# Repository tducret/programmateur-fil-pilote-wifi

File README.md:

Le programmateur fil pilote WiFi open source
============================================

Principe
--------
Avec de simples requêtes HTTP, vous allez pouvoir :
- **Contrôler vos chauffages électriques** (7 zones / 4 ordres fil pilote)
- **Récupérer votre consommation électrique** (et toutes les informations du compteur électrique)

Avantages :
- **Pas de serveur dédié nécessaire**
- **Intégration facile dans le tableau électrique**
- **Connexion WiFi** (pas de câble Ethernet à connecter)

Idées d'applications
--------------------
- Contrôle de la température de chaque pièce via votre box domotique
- Coupure du chauffage automatique en cas de consommation électrique trop importante (délestage)
- Lancement du chauffage en partant du travail à partir de votre smartphone
- Et bien d'autres...

Licence
-------
Les codes sources sont distribués sous la licence MIT
Les autres éléments sont distribués sous la licence [Creative Commons Attribution-NonCommercial-ShareAlike 4.0](https://creativecommons.org/licenses/by-nc-sa/4.0/)

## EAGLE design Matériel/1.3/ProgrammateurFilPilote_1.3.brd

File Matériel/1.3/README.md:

Version matérielle 1.3
=======================

Modifications
-------------
Cette version reprend toutes les caractéristiques de la version [initiale][1] en y ajoutant les fonctionnalités suivantes :

- Ajout d'un contrôleur d'entrées sortie I2C [MCP23017][10] pour libérer les I/O du Spark Core
- Possibilité de mettre deux types de relais dont un [avec contact NO + NF][5]
- Possibilité de mettre un emetteur récepteur sans fil de type [RFM12B][6], [RFM69CW][7], [RFM69HW][8] ou [RFM69CW][9] 433Mhz ou 868MHz
- Possibilité de mettre un [récepteur 433MHz][4] pour récupérer par exemple les trames des capteurs de température Orégon Scientific
- Ajout d'un connecteur I2C ET SPI pour des afficheurs OLED de type [I2C][2] ou [SPI][3]
- Ajout d'un connecteur de type Grove I2C
- Ajout d'une LED 3mm (déportable ou non) sur le boitier 
- Ajout de pin out disponibles sur toutes les pattes du Spark Core

Changements apportés dans la révision 1.3 vs 1.2 
- Ajout d'un étage a MOSFET pour la téléinfo, pour une meilleure compatibilité di signal téléinfo
- Ajout d'une RGB LED pour ESP8266
- Ajout d'un pont diviseur sur le recepteur 433MHZ pour transformer sa sortie 5V en 3V3 pour l'ESP8266
- Possibilité de mettre une base ESP8266 (NodeMCU) via cet [adaptateur][11]

Description Détaillée
=====================

**Schematic**  

**Boards**  
&nbsp;
&nbsp;

[1]: https://github.com/thibdct/programmateur-fil-pilote-wifi/blob/master/README.md
[2]: http://www.ebay.com/itm/291216700457
[3]: http://www.ebay.com/itm/141371873602
[4]: http://www.ebay.com/itm/290935235157
[5]: http://www.seeedstudio.com/depot/index.php?main_page=opl_info&opl_id=136

[6]: http://www.anarduino.com/details.jsp?pid=142
[7]: http://www.anarduino.com/details.jsp?pid=145
[8]: http://www.anarduino.com/details.jsp?pid=136
[9]: http://www.anarduino.com/details.jsp?pid=122
[10]: http://www.adafruit.com/product/732
[11]: https://github.com/hallard/Particle2NodeMCU

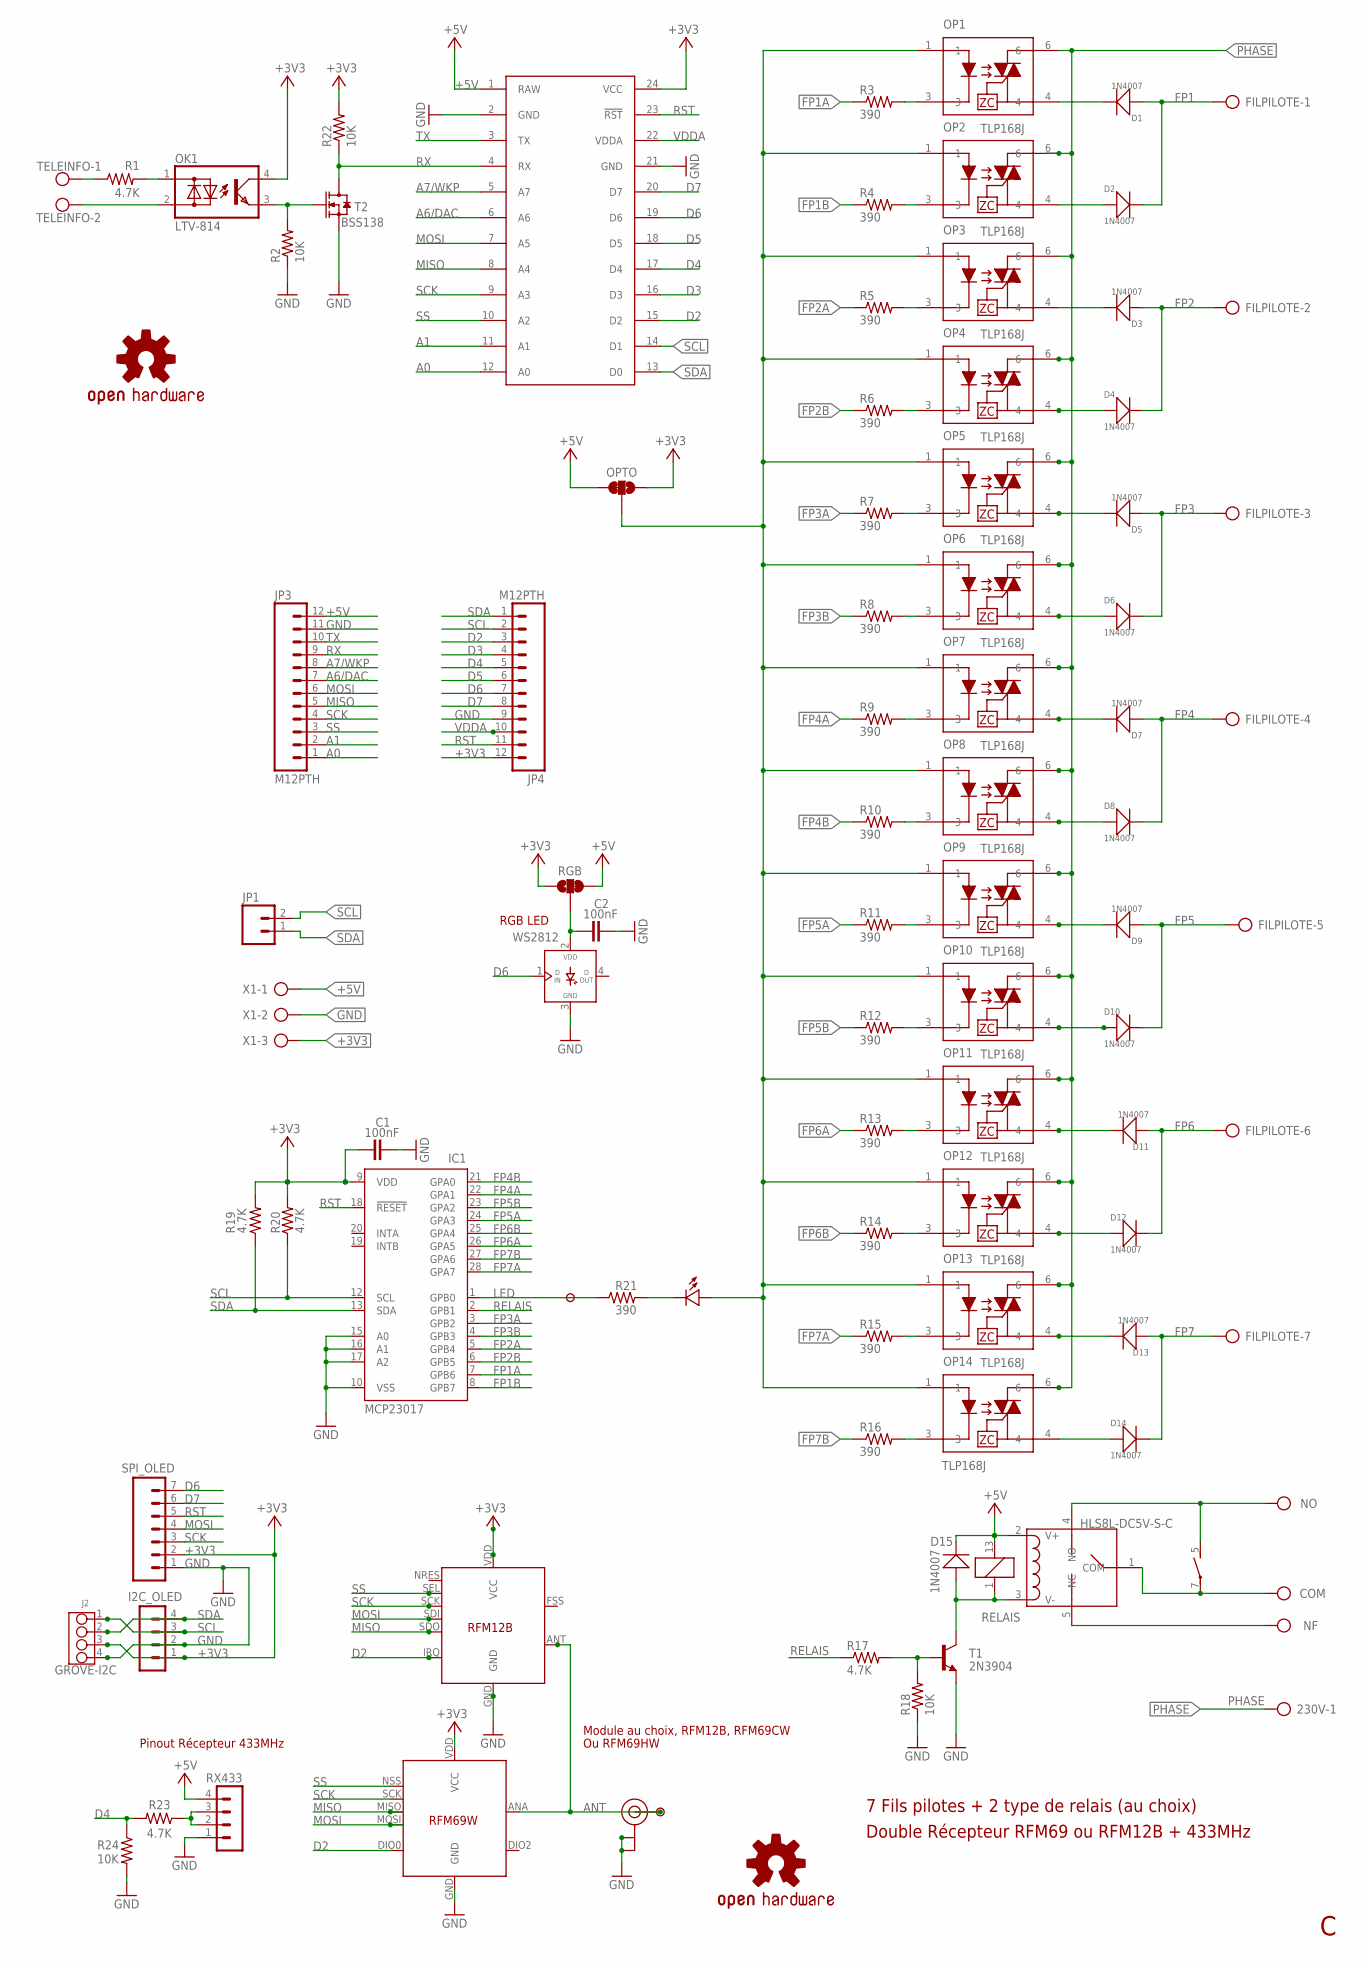
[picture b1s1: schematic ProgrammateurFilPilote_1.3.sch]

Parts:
230V: AK500/2
C1, C2: 100nF; 1206-CAP
D1, D2, D3, D4, D5, D6, D7, D8, D9, D10, D11, D12, D13, D14, D15: 1N4007; DO-214AC
FILPILOTE: AK500/7
I2C_OLED: CON_HEADER_1X04'SMALL''; M1X4
IC1: MCP23017; DIL28-3
J2: GROVE-I2C; 4P-2.0
JP1: M02PTH; 1X02
JP3, JP4: M12PTH; 1X12-SMALL-PADS
LED: LED3MM
LOGO1, LOGO2: OSHW-LOGOL; OSHW-LOGO-L
OK1: LTV-814; DIL4-SMD
OP1, OP2, OP3, OP4, OP5, OP6, OP7, OP8, OP9, OP10, OP11, OP12, OP13, OP14: TLP168J; MFSOP-4-HANDSOLDER
OPTO: JUMPER-PAD-3-2OF3_NC_BY_TRACE_LARGE; PAD-JUMPER-3-2OF3_NC_BY_TRACE_YES_SILK_LARGE
P1, P2: PADSMALL; PAD-SMALL
PARTICLE: Spark/Photon; SPARK_CORE
R1, R17, R19, R20, R23: 4.7K; 1206-RES
R2, R18, R22, R24: 10K; 1206-RES
R3, R4, R5, R6, R7, R8, R9, R10, R11, R12, R13, R14, R15, R16, R21: 390; 1206-RES
RELAIS: Relais G6D; G6D
RGB: JUMPER-PAD-3-2OF3_NC_BY_TRACE_SMALL; PAD-JUMPER-3-2OF3_NC_BY_TRACE_YES_SILK_FULL_BOX
RL: AK500/2
RX433: CON_HEADER_1X04'NO_LOCK'; 1X04_NO_LOCK
SPI_OLED: CON_HEADER_1X07'SMALL'; M1X7
SW1: HLS8L-DC5V-S-C; 5P-L19.0XW15.0XH15.0MM
T1: 2N3904; TO92-EBC
T2: BSS138; SOT23
TELEINFO: AK500/2
U$2: RFM12B; RFM12B-MINPADS
U$3: RFM69W; RFM69W-MINPADS
U-FL: U.FL
WS2812: RGB LED; WS2812-PTH
X1: AK500/3

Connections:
+3V3: C1.1, I2C_OLED.1, IC1.9 (VDD), J2.3, JP4.12, OK1.4 (C), OPTO.1, PARTICLE.24 (VCC), R19.2, R20.2, R22.2, RGB.1, SPI_OLED.2, U$2.VDD (VCC), U$3.VDD (VCC), X1.3
+5V: D15.2 (-), JP3.12, OPTO.3, PARTICLE.1 (RAW), RELAIS.13 (2), RGB.3, RX433.4, SW1.2 (V+), X1.1
A0: JP3.1, PARTICLE.12 (A0)
A1: JP3.2, PARTICLE.11 (A1)
A6/DAC: JP3.7, PARTICLE.6 (A6)
A7/WKP: JP3.8, PARTICLE.5 (A7)
ANT: P1.1, U$2.ANT, U$3.ANA (ANT), U-FL.3 (SIGNAL)
COM: RELAIS.7, RL.1, SW1.1 (COM)
D2: JP4.3, PARTICLE.15 (D2), U$2.IRQ, U$3.DIO0
D3: JP4.4, PARTICLE.16 (D3)
D4: JP4.5, PARTICLE.17 (D4), R23.2, R24.1
D5: JP4.6, PARTICLE.18 (D5)
D6: JP4.7, PARTICLE.19 (D6), SPI_OLED.7, WS2812.1 (DIN)
D7: JP4.8, PARTICLE.20 (D7), SPI_OLED.6
FP1: D1.1 (+), D2.2 (-), FILPILOTE.1
FP1A: IC1.7 (GPB6), R3.1
FP1B: IC1.8 (GPB7), R4.1
FP2: D3.1 (+), D4.2 (-), FILPILOTE.2
FP2A: IC1.5 (GPB4), R5.1
FP2B: IC1.6 (GPB5), R6.1
FP3: D5.1 (+), D6.2 (-), FILPILOTE.3
FP3A: IC1.3 (GPB2), R7.1
FP3B: IC1.4 (GPB3), R8.1
FP4: D7.1 (+), D8.2 (-), FILPILOTE.4
FP4A: IC1.22 (GPA1), R9.1
FP4B: IC1.21 (GPA0), R10.1
FP5: D9.1 (+), D10.2 (-), FILPILOTE.5
FP5A: IC1.24 (GPA3), R11.1
FP5B: IC1.23 (GPA2), R12.1
FP6: D11.1 (+), D12.2 (-), FILPILOTE.6
FP6A: IC1.26 (GPA5), R13.1
FP6B: IC1.25 (GPA4), R14.1
FP7: D13.1 (+), D14.2 (-), FILPILOTE.7
FP7A: IC1.28 (GPA7), R15.1
FP7B: IC1.27 (GPA6), R16.1
GND: C1.2, C2.2, I2C_OLED.2, IC1.10 (VSS), IC1.15 (A0), IC1.16 (A1), IC1.17 (A2), J2.4, JP3.11, JP4.9, PARTICLE.2 (GND), PARTICLE.21 (GND), R2.1, R18.1, R24.2, RX433.1, SPI_OLED.1, T1.E, T2.2 (S), U$2.GND, U$3.GND, U-FL.1 (GND), U-FL.2 (GND), WS2812.3 (GND), X1.2
LED: IC1.1 (GPB0), P2.1, R21.1
MISO: JP3.5, PARTICLE.8 (A4), U$2.SDO, U$3.MISO
MOSI: JP3.6, PARTICLE.7 (A5), SPI_OLED.4, U$2.SDI, U$3.MOSI
unnamed: D1.2 (-), OP1.4
unnamed: D2.1 (+), OP2.4
unnamed: OK1.2 (AC2), TELEINFO.2
unnamed: OK1.1 (AC1), R1.2
unnamed: R1.1, TELEINFO.1
unnamed: LED.MINUS, R21.2
unnamed: OP1.3, R3.2
unnamed: OP2.3, R4.2
unnamed: OP3.3, R5.2
unnamed: OP4.3, R6.2
unnamed: OP5.3, R7.2
unnamed: OP6.3, R8.2
unnamed: OP7.3, R9.2
unnamed: OP8.3, R10.2
unnamed: D15.1 (+), RELAIS.1, SW1.3 (V-), T1.C
unnamed: C2.1, RGB.2, WS2812.2 (VDD)
unnamed: OK1.3 (E), R2.2, T2.1 (G)
unnamed: OP9.3, R11.2
unnamed: LED.PLUS, OP1.1, OP2.1, OP3.1, OP4.1, OP5.1, OP6.1, OP7.1, OP8.1, OP9.1, OP10.1, OP11.1, OP12.1, OP13.1, OP14.1, OPTO.2
unnamed: R17.2, R18.2, T1.B
unnamed: D3.2 (-), OP3.4
unnamed: D5.2 (-), OP5.4
unnamed: D4.1 (+), OP4.4
unnamed: D7.2 (-), OP7.4
unnamed: D6.1 (+), OP6.4
unnamed: D8.1 (+), OP8.4
unnamed: OP10.3, R12.2
unnamed: OP14.3, R16.2
unnamed: D9.2 (-), OP9.4
unnamed: OP11.3, R13.2
unnamed: OP12.3, R14.2
unnamed: D10.1 (+), OP10.4
unnamed: D12.1 (+), OP12.4
NF: RL.2, SW1.5 (NC)
NO: 230V.2, RELAIS.5 (S), SW1.4 (NO)
PHASE: 230V.1, OP1.6, OP2.6, OP3.6, OP4.6, OP5.6, OP6.6, OP7.6, OP8.6, OP9.6, OP10.6, OP11.6, OP12.6, OP13.6, OP14.6
RELAIS: IC1.2 (GPB1), R17.1
RST: IC1.18 (!RESET), JP4.11, PARTICLE.23 (!RST), SPI_OLED.5
RX: JP3.9, PARTICLE.4 (RX), R22.1, T2.3 (D)
RX433: R23.1, RX433.2, RX433.3
S$1: D11.2 (-), OP11.4
S$3: D13.2 (-), OP13.4
S$5: OP13.3, R15.2
S$11: D14.1 (+), OP14.4
SCK: JP3.4, PARTICLE.9 (A3), SPI_OLED.3, U$2.SCK, U$3.SCK
SCL: I2C_OLED.3, IC1.12 (SCL), J2.1, JP1.2, JP4.2, PARTICLE.14 (D1), R20.1
SDA: I2C_OLED.4, IC1.13 (SDA), J2.2, JP1.1, JP4.1, PARTICLE.13 (D0), R19.1
SS: JP3.3, PARTICLE.10 (A2), U$2.SEL, U$3.NSS (SEL)
TX: JP3.10, PARTICLE.3 (TX)
VDDA: JP4.10, PARTICLE.22 (VDDA)

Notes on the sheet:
7 Fils pilotes + 2 type de relais (au choix)
Module au choix, RFM12B, RFM69CW
Ou RFM69HW
Pinout Récepteur 433MHz
Double Récepteur RFM69 ou RFM12B + 433MHz
RGB LED

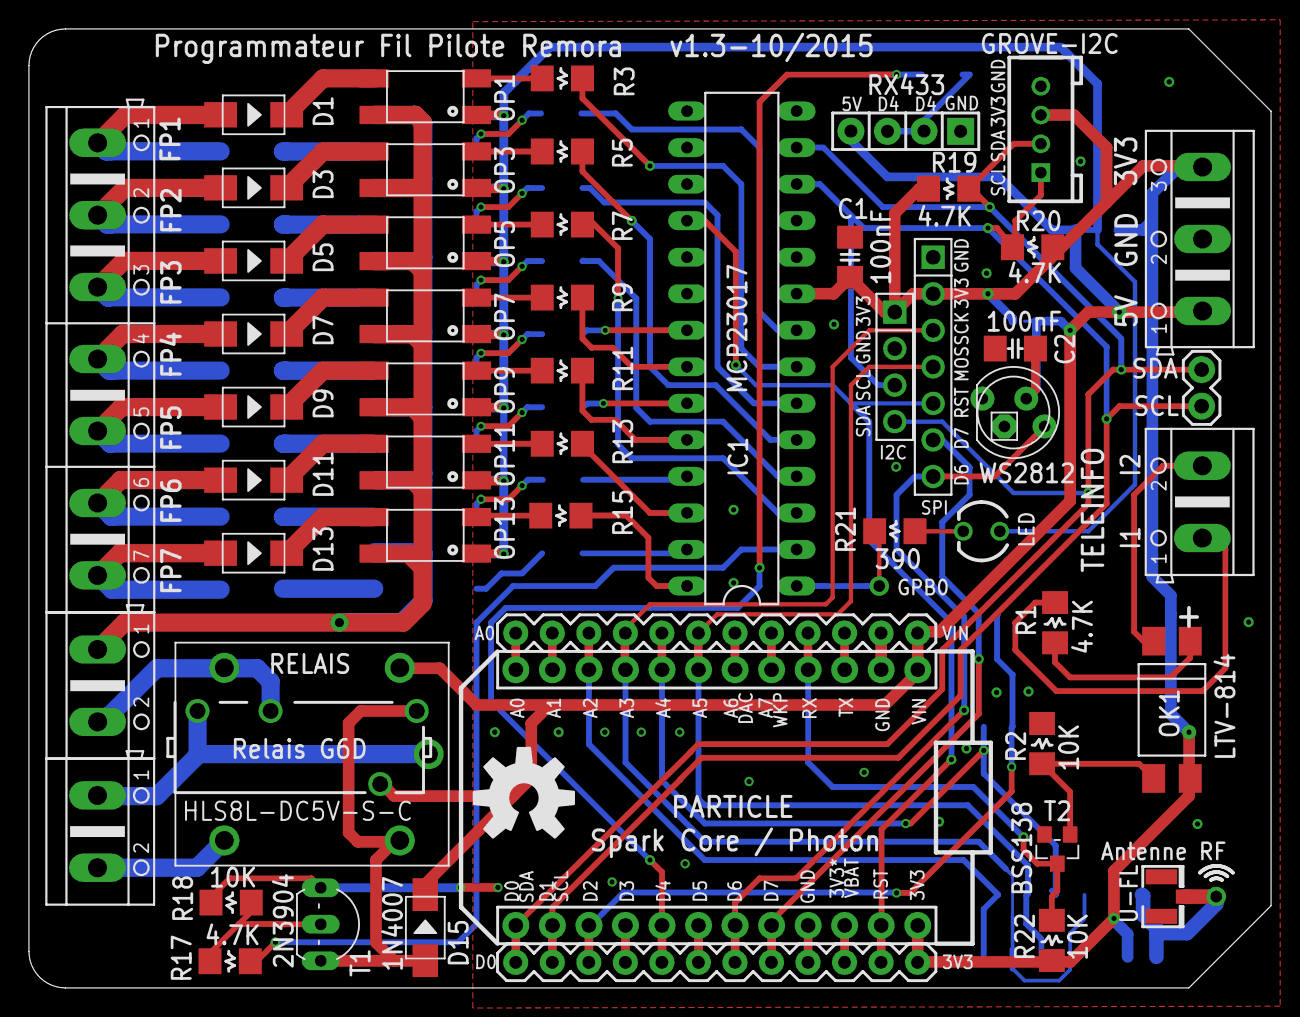
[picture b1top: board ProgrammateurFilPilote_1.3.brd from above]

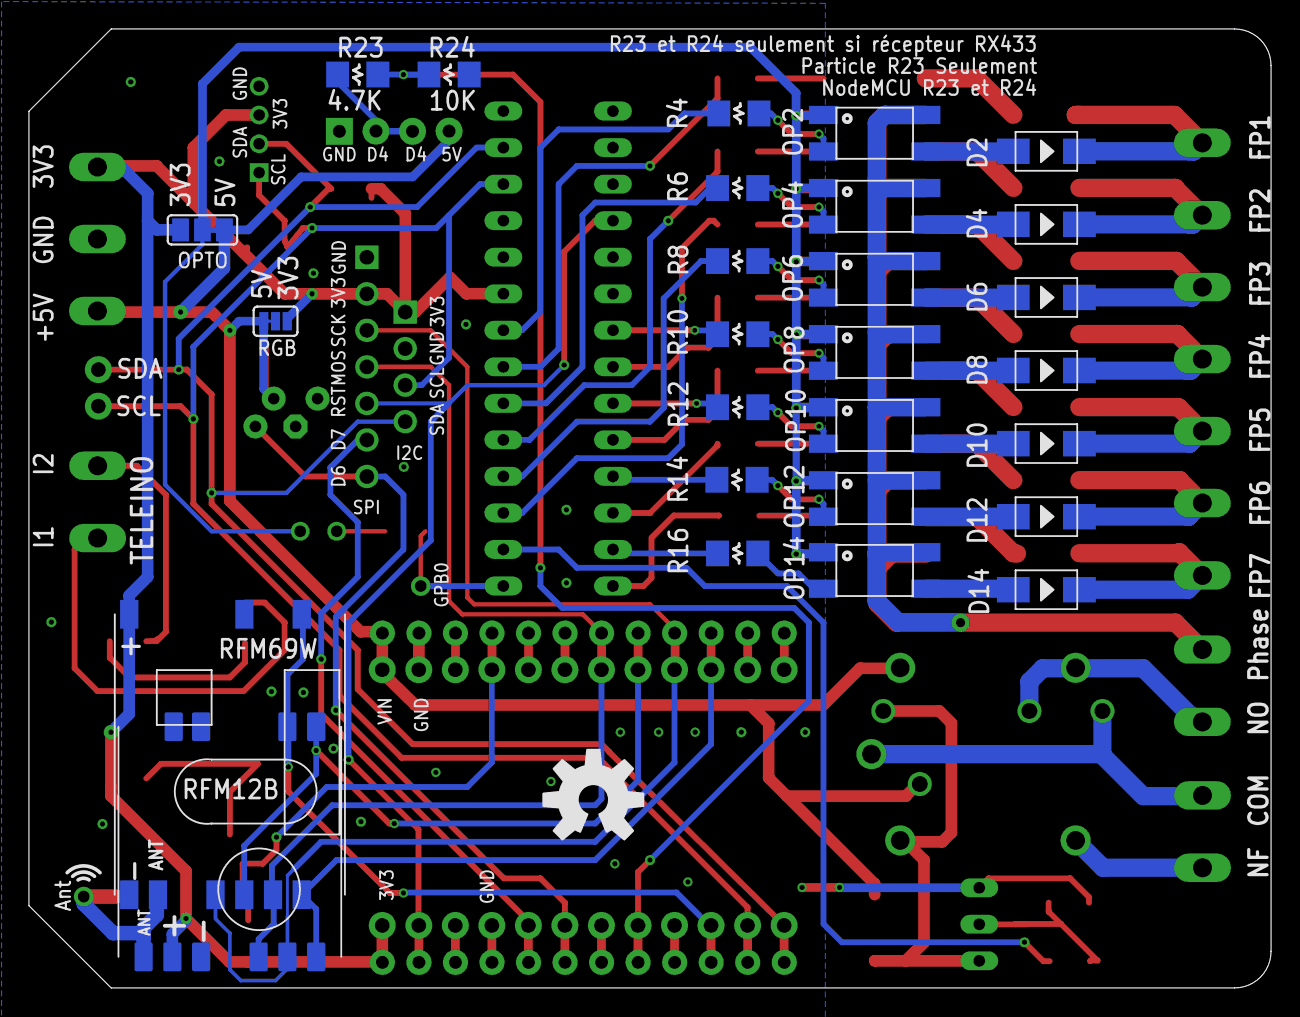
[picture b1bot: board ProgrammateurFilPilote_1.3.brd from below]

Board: 2 copper layers, 86.4 x 66.7 mm, 85 parts (28 on the bottom side), 89 nets.

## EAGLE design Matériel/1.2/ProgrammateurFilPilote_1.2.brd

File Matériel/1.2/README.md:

Version matérielle 1.2c
=======================

Modifications
-------------
Cette version reprend toutes les caractéristiques de la version [initiale][1] en y ajoutant les fonctionnalités suivantes :

- Ajout d'un contrôleur d'entrées sortie I2C [MCP23017][10] pour libérer les I/O du Spark Core
- Possibilité de mettre deux types de relais dont un [avec contact NO + NF][5]
- Possibilité de mettre un emetteur récepteur sans fil de type [RFM12B][6], [RFM69CW][7], [RFM69HW][8] ou [RFM69CW][9] 433Mhz ou 868MHz
- Possibilité de mettre un [récepteur 433MHz][4] pour récupérer par exemple les trames des capteurs de température Orégon Scientific
- Ajout d'un connecteur I2C ET SPI pour des afficheurs OLED de type [I2C][2] ou [SPI][3]
- Ajout d'un connecteur de type Grove I2C
- Ajout d'une LED 3mm (déportable ou non) sur le boitier 
- Ajout de pin out disponibles sur toutes les pattes du Spark Core

Changements apportés dans la révision 1.2c 
- Correction informations du silk au niveau du connecteur grove
- Déplacement connecteur grove pour ne pas géner en cas d'insertion un module grove
- Déplacement de la LED pour qu'elle ne soit plus située sous le LCD
- Agrandissement des PAD des optos pour une soudure plus aisée
- Inversion des plots 3.3V et GND afin de pouvoir souder un double plot uniquement (5V+GND), les triples étant moins facile à trouver et je suis pas certain que le 3.3V soit utilisé (mais il reste disponible)

Attention, deux erreurs étaient présentes sur le PCB 1.2 original (corrigées dans la revision 1.2c) :
- le dessin sur le PCB du connecteur grove est inversé, donc si vous souhaitez le souder, il faut le faire dans le sens inversé par rapport au dessin du PCB (mais toujours à souder sur le dessus).
- la diode D14 est inversée, il faut donc la souder dans le sens inverse de ce qui est indiqué sur le PCB

Description Détaillée
=====================

**Schematic**  

**Boards**  
&nbsp;
&nbsp;

[1]: https://github.com/thibdct/programmateur-fil-pilote-wifi/blob/master/README.md
[2]: http://www.ebay.com/itm/291216700457
[3]: http://www.ebay.com/itm/141371873602
[4]: http://www.ebay.com/itm/290935235157
[5]: http://www.seeedstudio.com/depot/index.php?main_page=opl_info&opl_id=136

[6]: http://www.anarduino.com/details.jsp?pid=142
[7]: http://www.anarduino.com/details.jsp?pid=145
[8]: http://www.anarduino.com/details.jsp?pid=136
[9]: http://www.anarduino.com/details.jsp?pid=122
[10]: http://www.adafruit.com/product/732

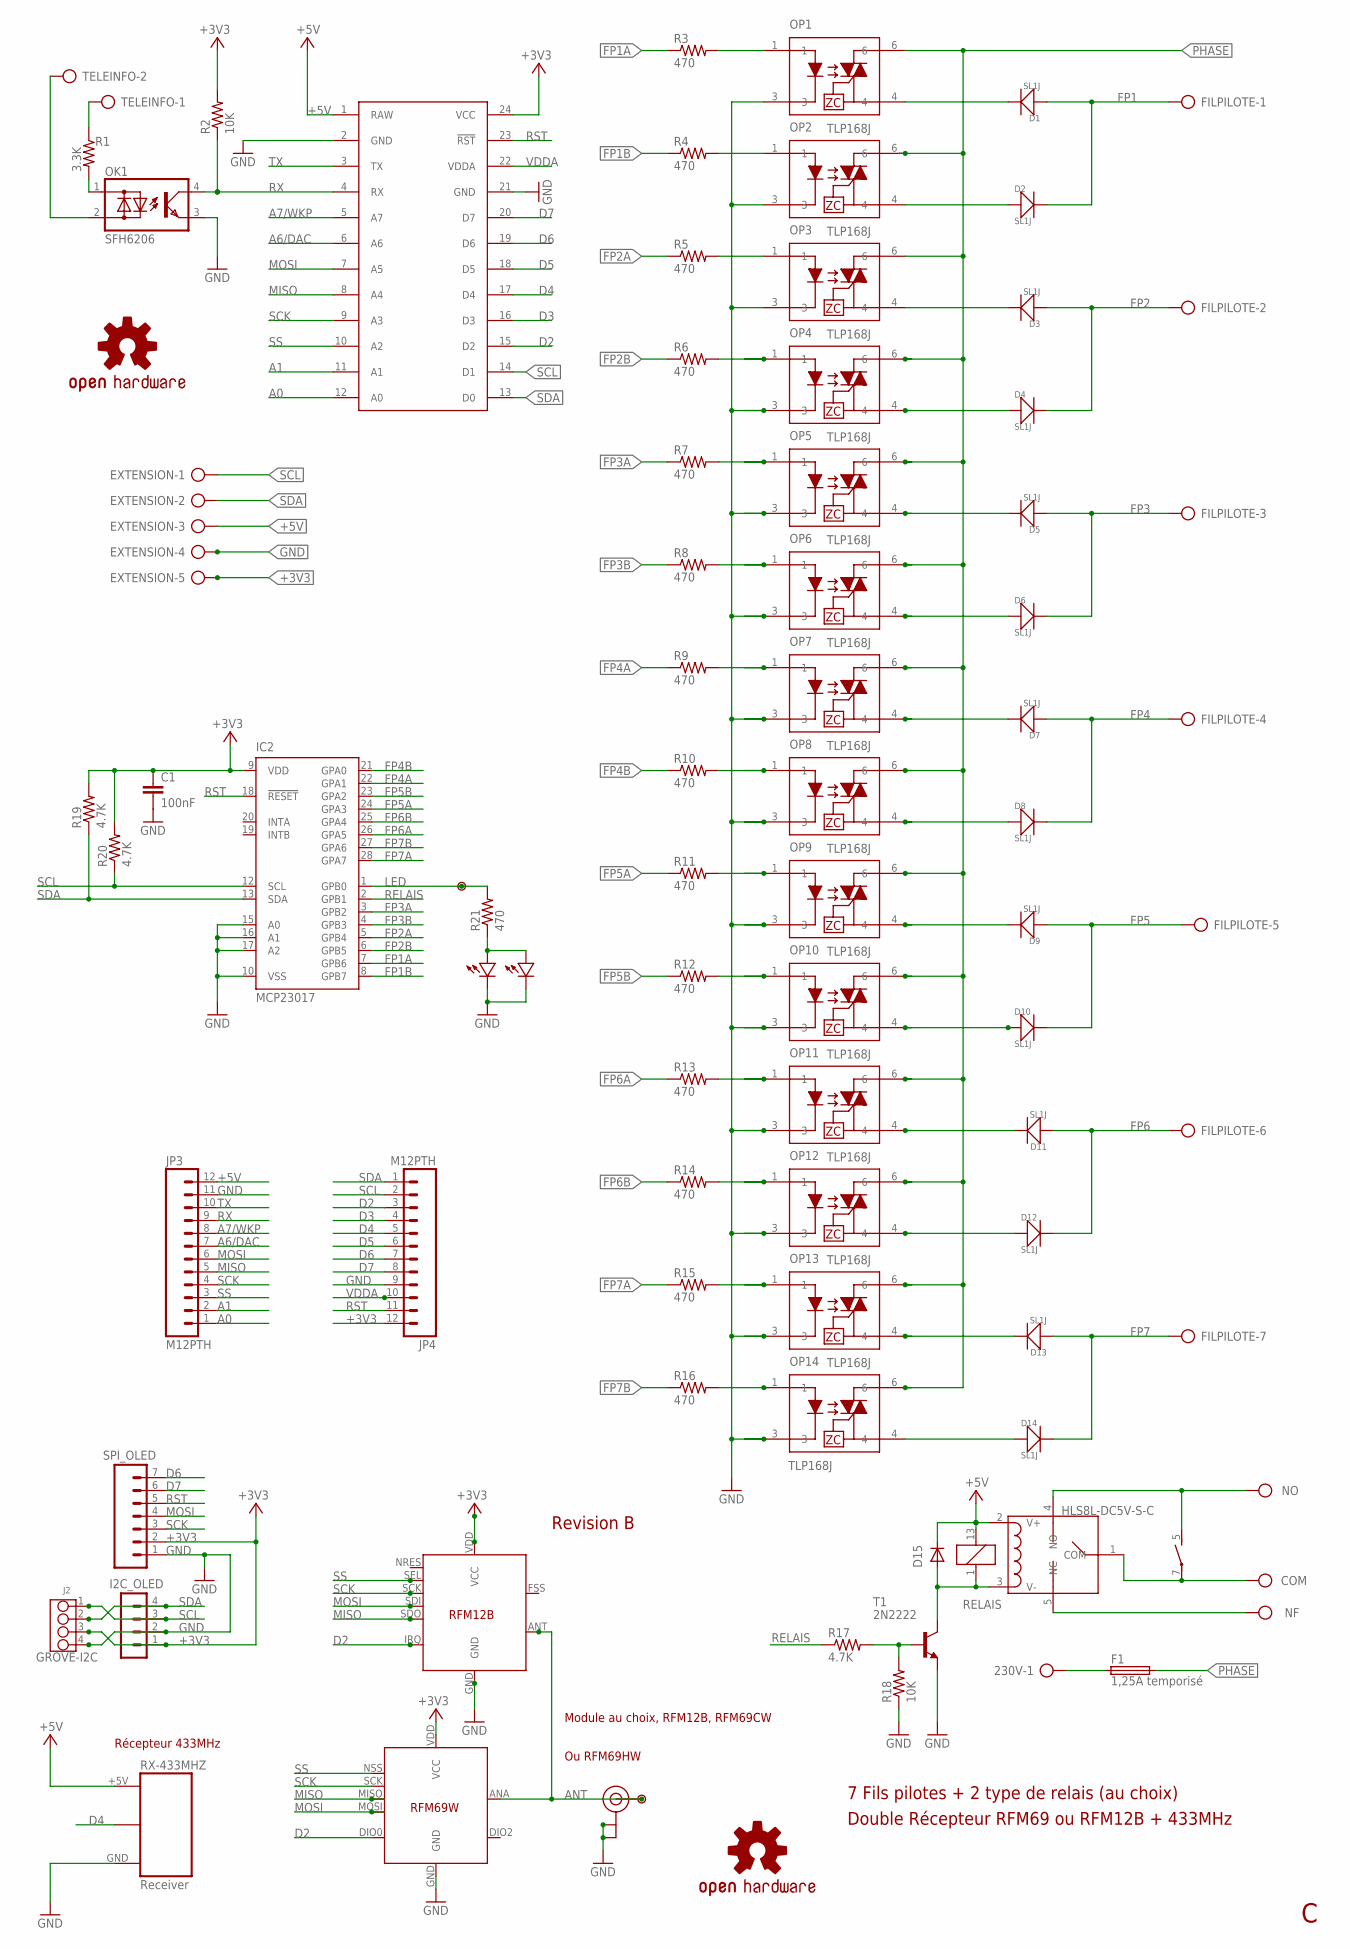
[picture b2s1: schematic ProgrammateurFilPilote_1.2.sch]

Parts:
230V: AK500/2
C1: 100nF; 1206-CAP
D1, D2, D3, D4, D5, D6, D7, D8, D9, D10, D11, D12, D13, D14: SL1J; DO-214AC
D15: CGRM4001-G; SOD-123_MINI-SMA
EXTENSION: AK500/5
F1: 1,25A temporisé; TE5
FILPILOTE: AK500/7
I2C_OLED: CON_HEADER_1X04'SMALL''; M1X4
IC2: MCP23017; DIL28-3
J2: GROVE-I2C; 4P-2.0
JP3, JP4: M12PTH; 1X12-SMALL-PADS
L: LED0805-LARGE; 0805-LED-LARGEPADS
LED: LED3MMNOSILK; LED3MM_NOSILK
LOGO1, LOGO2: OSHW-LOGOL; OSHW-LOGO-L
OK1: SFH6206; DIL4-SMD
OP1, OP2, OP3, OP4, OP5, OP6, OP7, OP8, OP9, OP10, OP11, OP12, OP13, OP14: TLP168J; MFSOP-4-HANDSOLDER
P1, P2: PADSMALL; PAD-SMALL
R1: 3.3K; 1206-RES
R2, R18: 10K; 1206-RES
R3, R4, R5, R6, R7, R8, R9, R10, R11, R12, R13, R14, R15, R16, R21: 470; 1206-RES
R17, R19, R20: 4.7K; 1206-RES
RELAIS: Relais G6D; G6D
RL: AK500/2
RX-433MHZ: Receiver; RF-LINK_RX
SPARKCORE: SPARK_CORECORE; SPARK_CORE
SPI_OLED: CON_HEADER_1X07'SMALL'; M1X7
SW1: HLS8L-DC5V-S-C; 5P-L19.0XW15.0XH15.0MM
T1: 2N2222; TO92-EBC
TELEINFO: AK500/2
U$2: RFM12B; RFM12B-MINPADS
U$3: RFM69W; RFM69W-MINPADS
U-FL: U.FL

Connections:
+3V3: C1.1, EXTENSION.5, I2C_OLED.1, IC2.9 (VDD), J2.3, JP4.12, R2.2, R19.2, R20.2, SPARKCORE.24 (VCC), SPI_OLED.2, U$2.VDD (VCC), U$3.VDD (VCC)
+5V: D15.C, EXTENSION.3, JP3.12, RELAIS.13 (2), RX-433MHZ.+5V, SPARKCORE.1 (RAW), SW1.2 (V+)
A0: JP3.1, SPARKCORE.12 (A0)
A1: JP3.2, SPARKCORE.11 (A1)
A6/DAC: JP3.7, SPARKCORE.6 (A6)
A7/WKP: JP3.8, SPARKCORE.5 (A7)
ANT: P1.1, U$2.ANT, U$3.ANA (ANT), U-FL.3 (SIGNAL)
COM: RELAIS.7, RL.1, SW1.1 (COM)
D2: JP4.3, SPARKCORE.15 (D2), U$2.IRQ, U$3.DIO0
D3: JP4.4, SPARKCORE.16 (D3)
D4: JP4.5, RX-433MHZ.DATA@1 (DATA), RX-433MHZ.DATA@2 (DATA), SPARKCORE.17 (D4)
D5: JP4.6, SPARKCORE.18 (D5)
D6: JP4.7, SPARKCORE.19 (D6), SPI_OLED.7
D7: JP4.8, SPARKCORE.20 (D7), SPI_OLED.6
FP1: D1.1 (+), D2.2 (-), FILPILOTE.1
FP1A: IC2.7 (GPB6), R3.1
FP1B: IC2.8 (GPB7), R4.1
FP2: D3.1 (+), D4.2 (-), FILPILOTE.2
FP2A: IC2.5 (GPB4), R5.1
FP2B: IC2.6 (GPB5), R6.1
FP3: D5.1 (+), D6.2 (-), FILPILOTE.3
FP3A: IC2.3 (GPB2), R7.1
FP3B: IC2.4 (GPB3), R8.1
FP4: D7.1 (+), D8.2 (-), FILPILOTE.4
FP4A: IC2.22 (GPA1), R9.1
FP4B: IC2.21 (GPA0), R10.1
FP5: D9.1 (+), D10.2 (-), FILPILOTE.5
FP5A: IC2.24 (GPA3), R11.1
FP5B: IC2.23 (GPA2), R12.1
FP6: D11.1 (+), D12.2 (-), FILPILOTE.6
FP6A: IC2.26 (GPA5), R13.1
FP6B: IC2.25 (GPA4), R14.1
FP7: D13.1 (+), D14.2 (-), FILPILOTE.7
FP7A: IC2.28 (GPA7), R15.1
FP7B: IC2.27 (GPA6), R16.1
GND: C1.2, EXTENSION.4, I2C_OLED.2, IC2.10 (VSS), IC2.15 (A0), IC2.16 (A1), IC2.17 (A2), J2.4, JP3.11, JP4.9, L.MINUS, LED.MINUS, OK1.3 (E), OP1.3, OP2.3, OP3.3, OP4.3, OP5.3, OP6.3, OP7.3, OP8.3, OP9.3, OP10.3, OP11.3, OP12.3, OP13.3, OP14.3, R18.1, RX-433MHZ.GND, SPARKCORE.2 (GND), SPARKCORE.21 (GND), SPI_OLED.1, T1.E, U$2.GND, U$3.GND, U-FL.1 (GND), U-FL.2 (GND)
LED: IC2.1 (GPB0), P2.1, R21.2
MISO: JP3.5, SPARKCORE.8 (A4), U$2.SDO, U$3.MISO
MOSI: JP3.6, SPARKCORE.7 (A5), SPI_OLED.4, U$2.SDI, U$3.MOSI
unnamed: D1.2 (-), OP1.4
unnamed: D2.1 (+), OP2.4
unnamed: OK1.2 (AC2), TELEINFO.2
unnamed: OK1.1 (AC1), R1.2
unnamed: R1.1, TELEINFO.1
unnamed: L.PLUS, LED.PLUS, R21.1
unnamed: OP1.1, R3.2
unnamed: OP2.1, R4.2
unnamed: OP3.1, R5.2
unnamed: OP4.1, R6.2
unnamed: OP5.1, R7.2
unnamed: OP6.1, R8.2
unnamed: OP7.1, R9.2
unnamed: OP8.1, R10.2
unnamed: D15.A, RELAIS.1, SW1.3 (V-), T1.C
unnamed: 230V.1, F1.1
unnamed: OP9.1, R11.2
unnamed: R17.2, R18.2, T1.B
unnamed: D3.2 (-), OP3.4
unnamed: D5.2 (-), OP5.4
unnamed: D4.1 (+), OP4.4
unnamed: D7.2 (-), OP7.4
unnamed: D6.1 (+), OP6.4
unnamed: D8.1 (+), OP8.4
unnamed: OP10.1, R12.2
unnamed: OP14.1, R16.2
unnamed: D9.2 (-), OP9.4
unnamed: OP11.1, R13.2
unnamed: OP12.1, R14.2
unnamed: D10.1 (+), OP10.4
unnamed: D12.1 (+), OP12.4
NF: RL.2, SW1.5 (NC)
NO: 230V.2, RELAIS.5 (S), SW1.4 (NO)
PHASE: F1.2, OP1.6, OP2.6, OP3.6, OP4.6, OP5.6, OP6.6, OP7.6, OP8.6, OP9.6, OP10.6, OP11.6, OP12.6, OP13.6, OP14.6
RELAIS: IC2.2 (GPB1), R17.1
RST: IC2.18 (!RESET), JP4.11, SPARKCORE.23 (!RST), SPI_OLED.5
RX: JP3.9, OK1.4 (C), R2.1, SPARKCORE.4 (RX)
S$1: D11.2 (-), OP11.4
S$3: D13.2 (-), OP13.4
S$5: OP13.1, R15.2
S$11: D14.1 (+), OP14.4
SCK: JP3.4, SPARKCORE.9 (A3), SPI_OLED.3, U$2.SCK, U$3.SCK
SCL: EXTENSION.1, I2C_OLED.3, IC2.12 (SCL), J2.1, JP4.2, R20.1, SPARKCORE.14 (D1)
SDA: EXTENSION.2, I2C_OLED.4, IC2.13 (SDA), J2.2, JP4.1, R19.1, SPARKCORE.13 (D0)
SS: JP3.3, SPARKCORE.10 (A2), U$2.SEL, U$3.NSS (SEL)
TX: JP3.10, SPARKCORE.3 (TX)
VDDA: JP4.10, SPARKCORE.22 (VDDA)

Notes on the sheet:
7 Fils pilotes + 2 type de relais (au choix)
Module au choix, RFM12B, RFM69CW
Ou RFM69HW
Récepteur 433MHz
Double Récepteur RFM69 ou RFM12B + 433MHz
Revision B

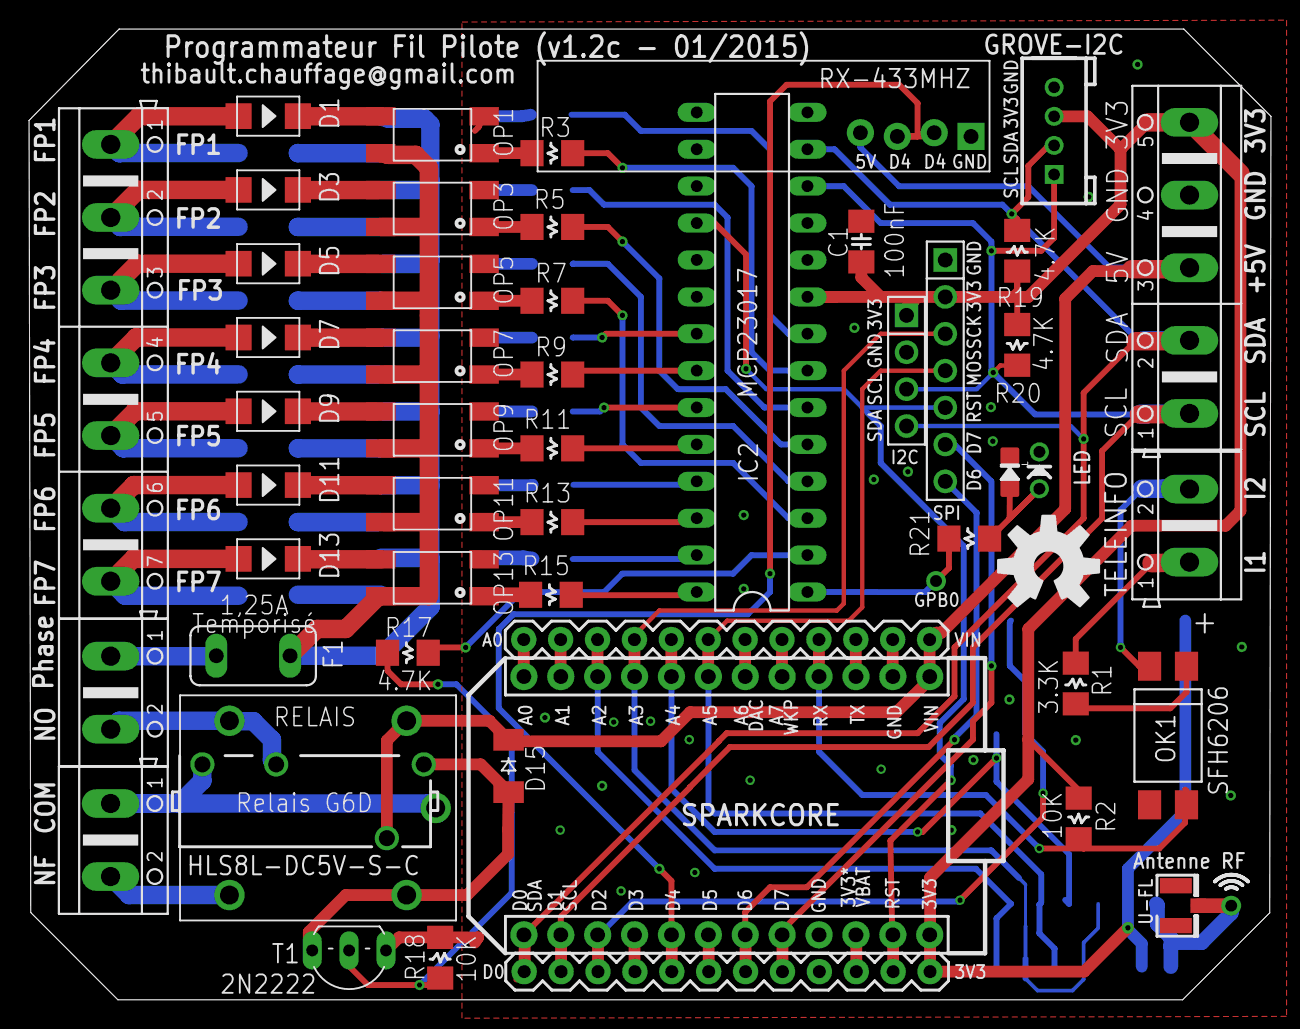
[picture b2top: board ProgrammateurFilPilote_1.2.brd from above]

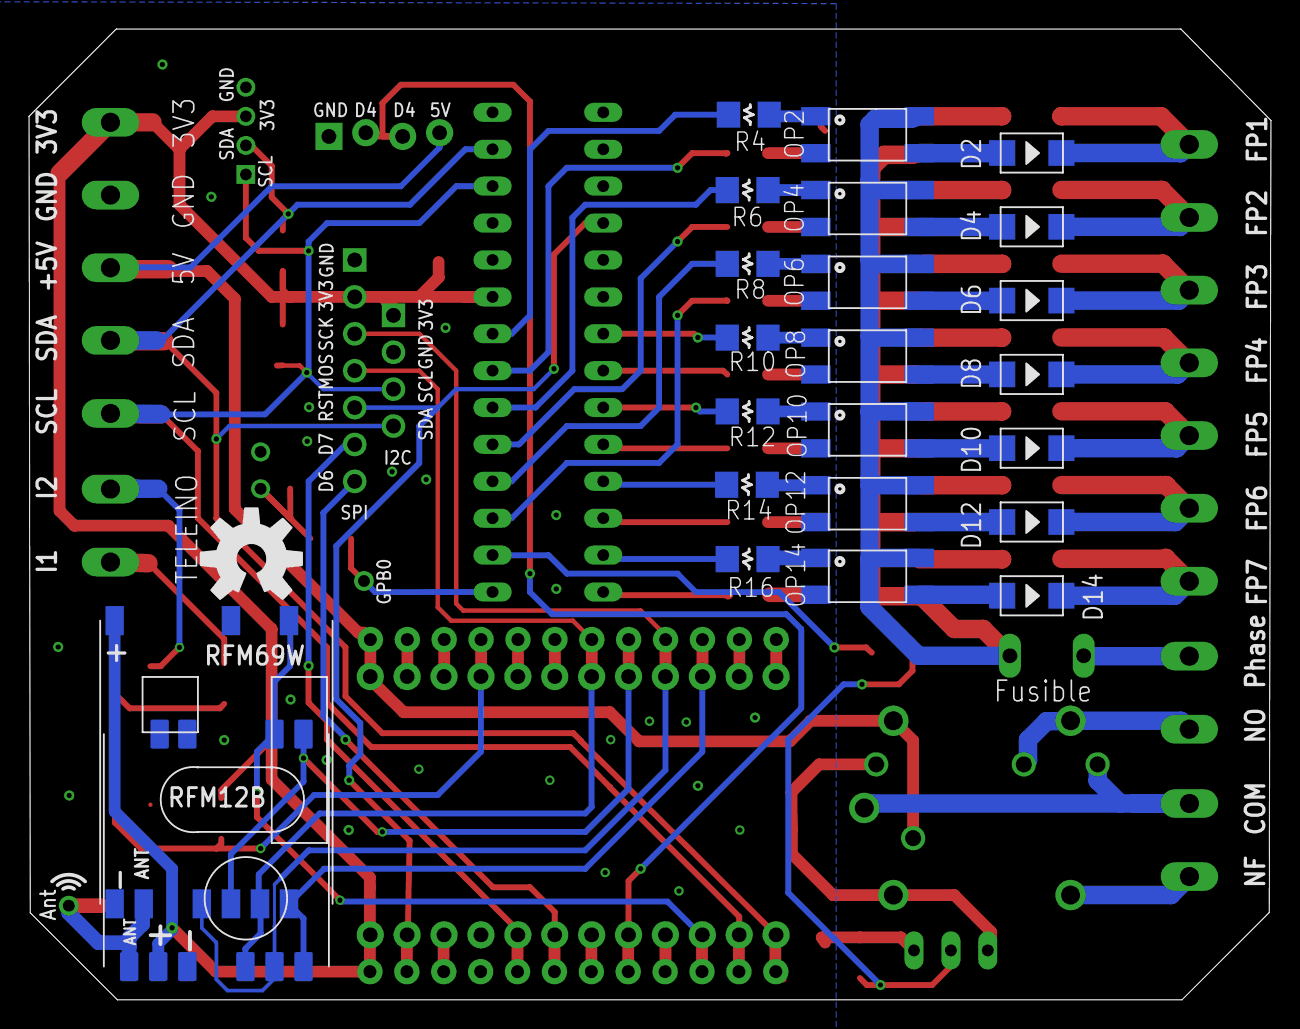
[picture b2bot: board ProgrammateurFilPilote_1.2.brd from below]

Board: 2 copper layers, 85.5 x 66.8 mm, 78 parts (24 on the bottom side), 86 nets.

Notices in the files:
parts and their libraries:
microbuilder: This work is placed in the public domain, and may be freely used for commercial and non-commercial work with the following conditions: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
SparkFun-Aesthetics: Licensing: Creative Commons ShareAlike 4.0 International - https://creativecommons.org/licenses/by-sa/4.0
